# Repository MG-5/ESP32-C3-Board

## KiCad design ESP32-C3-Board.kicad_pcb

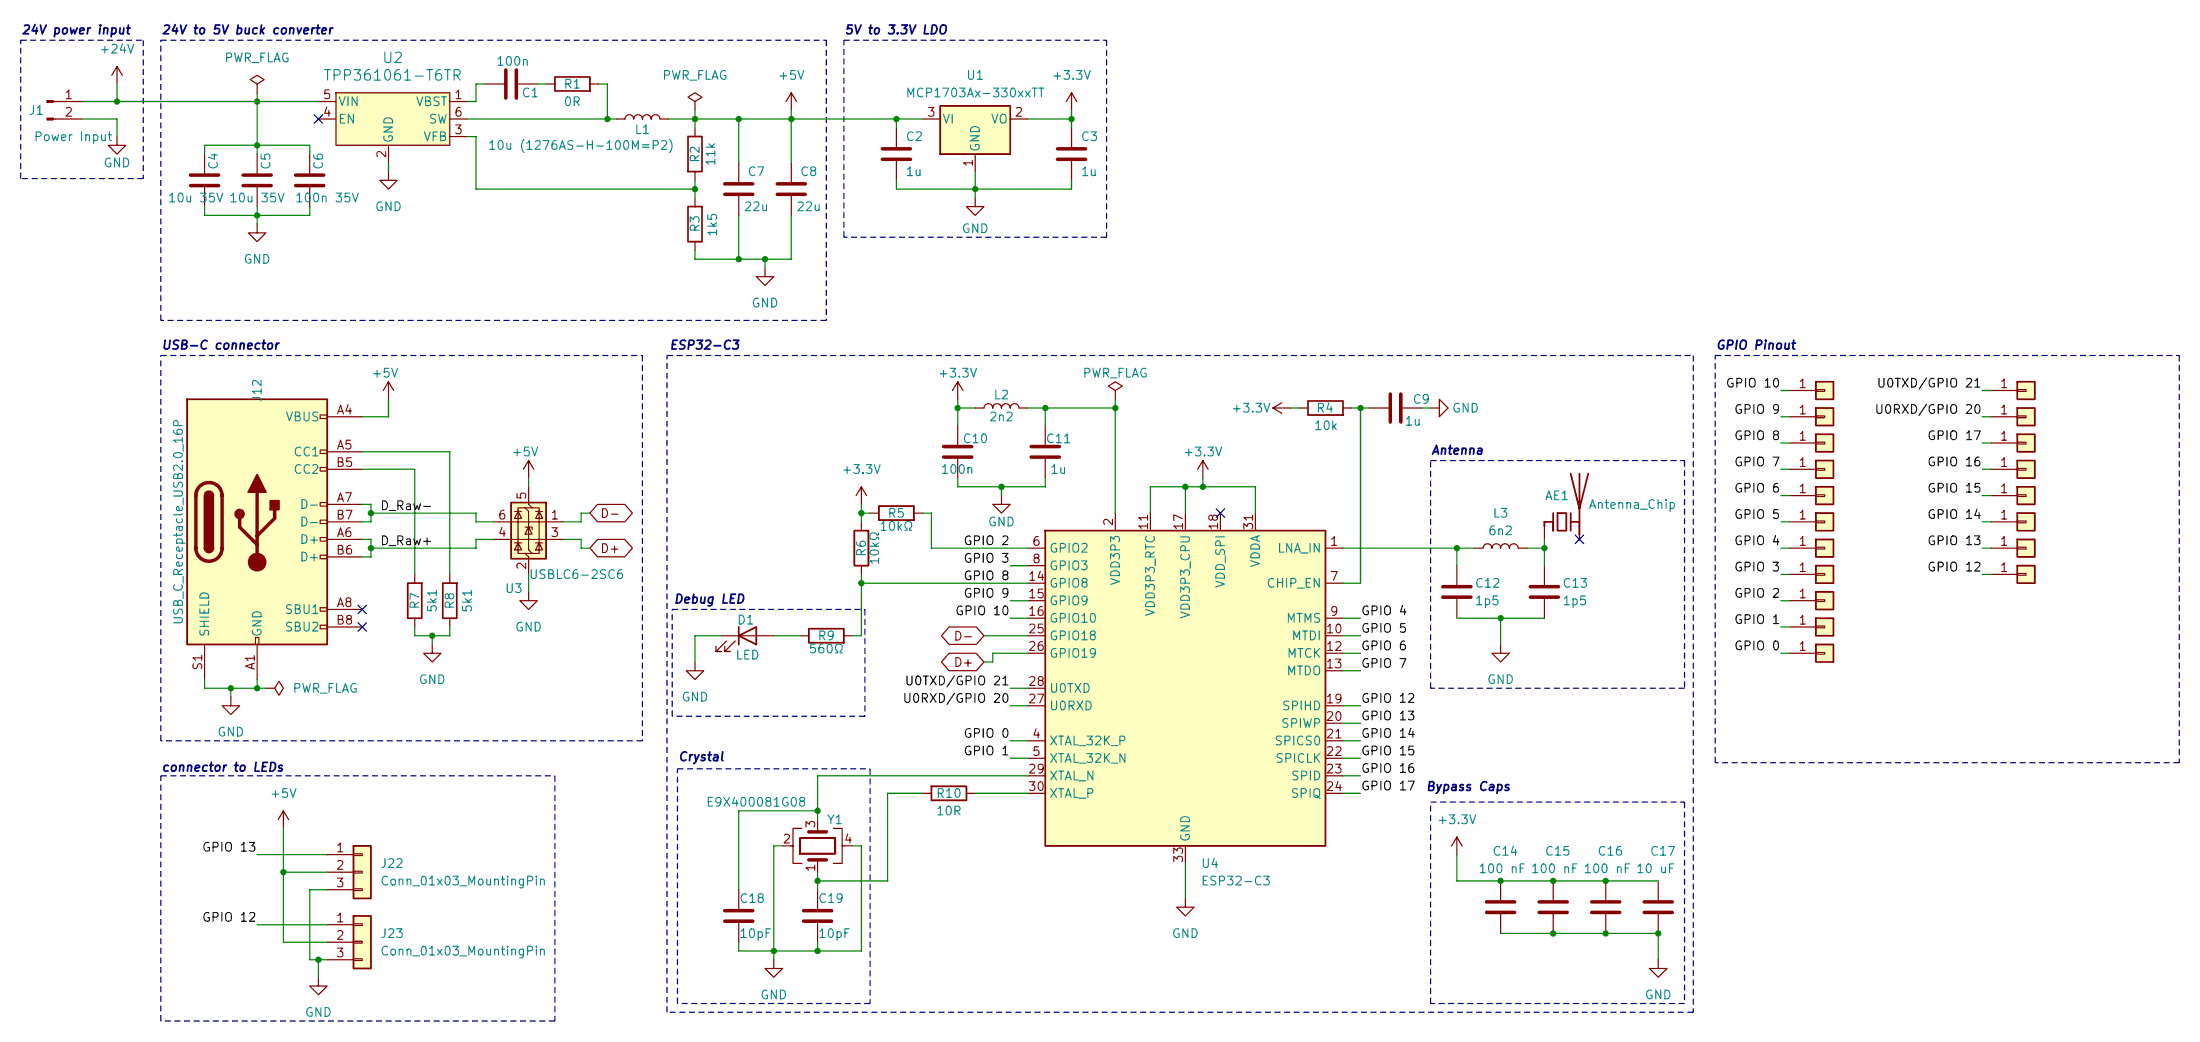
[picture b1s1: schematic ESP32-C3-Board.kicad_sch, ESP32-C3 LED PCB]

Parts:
AE1: Antenna_Chip; Johanson_2450AT43F0100
C1, C10: 100n; C_0603_1608Metric_Pad1.08x0.95mm_HandSolder
C2, C3, C9, C11: 1u; C_0603_1608Metric_Pad1.08x0.95mm_HandSolder
C4, C5: 10u 35V; C_0603_1608Metric_Pad1.08x0.95mm_HandSolder
C6: 100n 35V; C_0603_1608Metric_Pad1.08x0.95mm_HandSolder
C7, C8: 22u; C_0805_2012Metric_Pad1.18x1.45mm_HandSolder
C12, C13: 1p5; C_0402_1005Metric_Pad0.74x0.62mm_HandSolder
C14, C15, C16: 100 nF; C_0603_1608Metric_Pad1.08x0.95mm_HandSolder
C17: 10 uF; C_0603_1608Metric_Pad1.08x0.95mm_HandSolder
C18, C19: 10pF; C_0402_1005Metric_Pad0.74x0.62mm_HandSolder
D1: LED; LED_0805_2012Metric_Pad1.15x1.40mm_HandSolder
J1: Power Input; Molex_PicoBlade_53047-0210_1x02_P1.25mm_Vertical
J2, J3, J4, J5, J6, J7, J8, J9, J10, J11, J13, J14, J15, J16, J17, J18, J19, J20, J21: Conn_01x06; 01_P2.00mm
J12: USB_C_Receptacle_USB2.0_16P; USB_C_Receptacle_Palconn_UTC16-G
J22, J23: Conn_01x03_MountingPin; Molex_PicoBlade_53047-0310_1x03_P1.25mm_Vertical
L1: 10u (1276AS-H-100M=P2); L_1210_3225Metric_Pad1.42x2.65mm_HandSolder
L2: 2n2; L_0603_1608Metric
L3: 6n2; L_0402_1005Metric_Pad0.77x0.64mm_HandSolder
R1: 0R; R_0603_1608Metric_Pad0.98x0.95mm_HandSolder
R2: 11k; R_0603_1608Metric_Pad0.98x0.95mm_HandSolder
R3: 1k5; R_0603_1608Metric_Pad0.98x0.95mm_HandSolder
R4: 10k; R_0603_1608Metric_Pad0.98x0.95mm_HandSolder
R5, R6: 10kΩ; R_0603_1608Metric_Pad0.98x0.95mm_HandSolder
R7, R8: 5k1; R_0603_1608Metric_Pad0.98x0.95mm_HandSolder
R9: 560Ω; R_0603_1608Metric_Pad0.98x0.95mm_HandSolder
R10: 10R; R_0603_1608Metric_Pad0.98x0.95mm_HandSolder
U1: MCP1703Ax-330xxTT; SOT-23
U2: TPP361061-T6TR; SOT-23-6
U3: USBLC6-2SC6; SOT-23-6
U4: ESP32-C3; QFN-32-1EP_5x5mm_P0.5mm_EP3.7x3.7mm
Y1: E9X400081G08; Crystal_SMD_2016-4Pin_2.0x1.6mm

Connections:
+3.3V: C3.1, C10.1, C14.1, C15.1, C16.1, C17.1, L2.1, R4.1, R5.1, R6.2, U1.2 (VO), U4.11 (VDD3P3_RTC), U4.17 (VDD3P3_CPU), U4.31 (VDDA), U4.32 (VDDA)
+5V: C2.1, C7.2, C8.2, J12.A4 (VBUS), J12.A9 (VBUS), J12.B4 (VBUS), J12.B9 (VBUS), J22.2, J23.2, L1.1, R2.1, U1.3 (VI), U3.5 (VBUS)
+24V: C4.2, C5.2, C6.2, J1.1, U2.5 (VIN)
/D_Raw+: J12.A6 (D+), J12.B6 (D+), U3.4 (I/O2)
/D_Raw-: J12.A7 (D-), J12.B7 (D-), U3.6 (I/O1)
/GPIO 0: J21.1, U4.4 (XTAL_32K_P)
/GPIO 1: J20.1, U4.5 (XTAL_32K_N)
/GPIO 2: J19.1, R5.2, U4.6 (GPIO2)
/GPIO 3: J17.1, U4.8 (GPIO3)
/GPIO 4: J15.1, U4.9 (MTMS)
/GPIO 5: J13.1, U4.10 (MTDI)
/GPIO 6: J10.1, U4.12 (MTCK)
/GPIO 7: J8.1, U4.13 (MTDO)
/GPIO 8: J6.1, R6.1, R9.2, U4.14 (GPIO8)
/GPIO 9: J4.1, U4.15 (GPIO9)
/GPIO 10: J2.1, U4.16 (GPIO10)
/GPIO 12: J18.1, J23.1, U4.19 (SPIHD)
/GPIO 13: J16.1, J22.1, U4.20 (SPIWP)
/GPIO 14: J14.1, U4.21 (SPICS0)
/GPIO 15: J11.1, U4.22 (SPICLK)
/GPIO 16: J9.1, U4.23 (SPID)
/GPIO 17: J7.1, U4.24 (SPIQ)
/U0RXD/GPIO 20: J5.1, U4.27 (U0RXD)
/U0TXD/GPIO 21: J3.1, U4.28 (U0TXD)
D+: U3.3 (I/O2), U4.26 (GPIO19)
D-: U3.1 (I/O1), U4.25 (GPIO18)
GND: C2.2, C3.2, C4.1, C5.1, C6.1, C7.1, C8.1, C9.2, C10.2, C11.2, C12.2, C13.2, C14.2, C15.2, C16.2, C17.2, C18.2, C19.2, D1.1 (K), J1.2, J12.A1 (GND), J12.A12 (GND), J12.B1 (GND), J12.B12 (GND), J12.S1 (SHIELD), J22.3, J23.3, R3.1, R7.1, R8.1, U1.1 (GND), U2.2 (GND), U3.2 (GND), U4.33 (GND), Y1.2, Y1.4
unnamed: AE1.1 (FEED), C13.1, L3.2
unnamed: C1.2, R1.1
unnamed: C11.1, L2.2, U4.2 (VDD3P3), U4.3 (VDD3P3)
unnamed: C19.1, R10.2, Y1.1
unnamed: D1.2 (A), R9.1
unnamed: J12.A5 (CC1), R8.2
unnamed: J12.B5 (CC2), R7.2
unnamed: L1.2, R1.2, U2.6 (SW)
unnamed: C1.1, U2.1 (VBST)
unnamed: R2.2, R3.2, U2.3 (VFB)
unnamed: C9.1, R4.2, U4.7 (CHIP_EN)
unnamed: C12.1, L3.1, U4.1 (LNA_IN)
unnamed: C18.1, U4.29 (XTAL_N), Y1.3
unnamed: R10.1, U4.30 (XTAL_P)

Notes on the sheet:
Antenna
GPIO Pinout
Bypass Caps
Crystal
24V to 5V buck converter
USB-C connector
connector to LEDs
Debug LED
ESP32-C3
5V to 3.3V LDO
24V power input

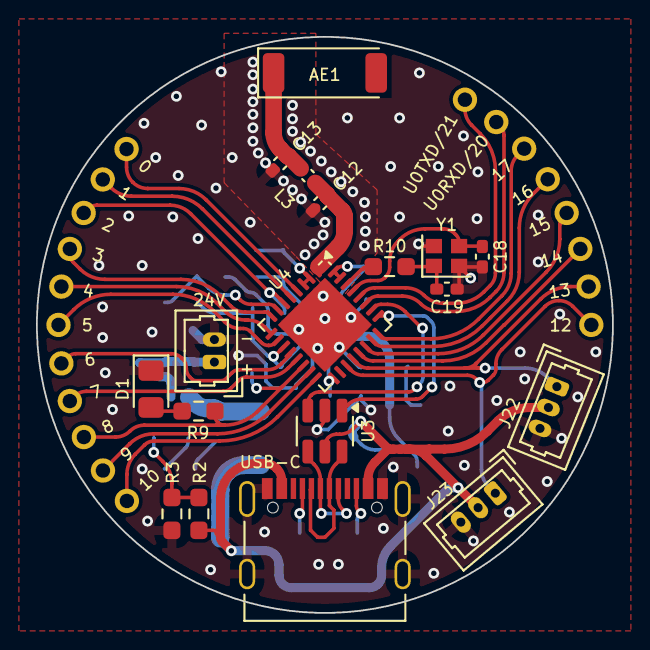
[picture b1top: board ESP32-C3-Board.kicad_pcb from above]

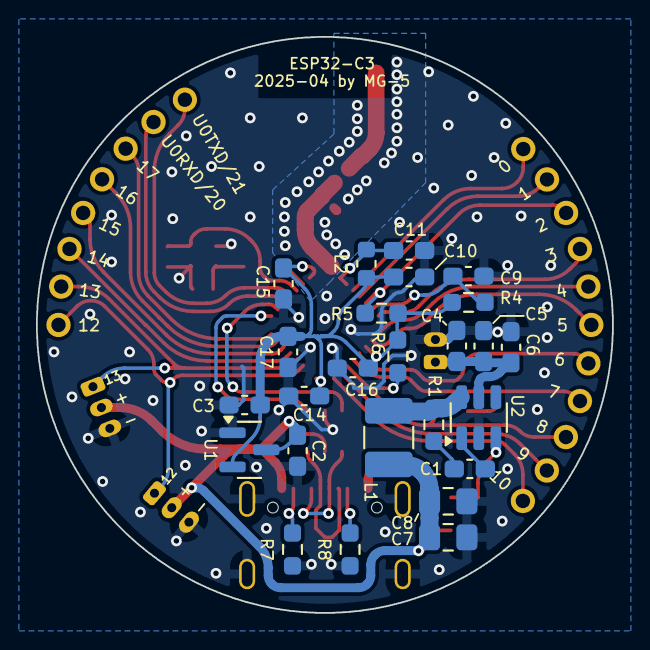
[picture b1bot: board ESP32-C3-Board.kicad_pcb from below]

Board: 2 copper layers, 32.0 x 32.0 mm, 62 parts (25 on the bottom side), 41 nets.

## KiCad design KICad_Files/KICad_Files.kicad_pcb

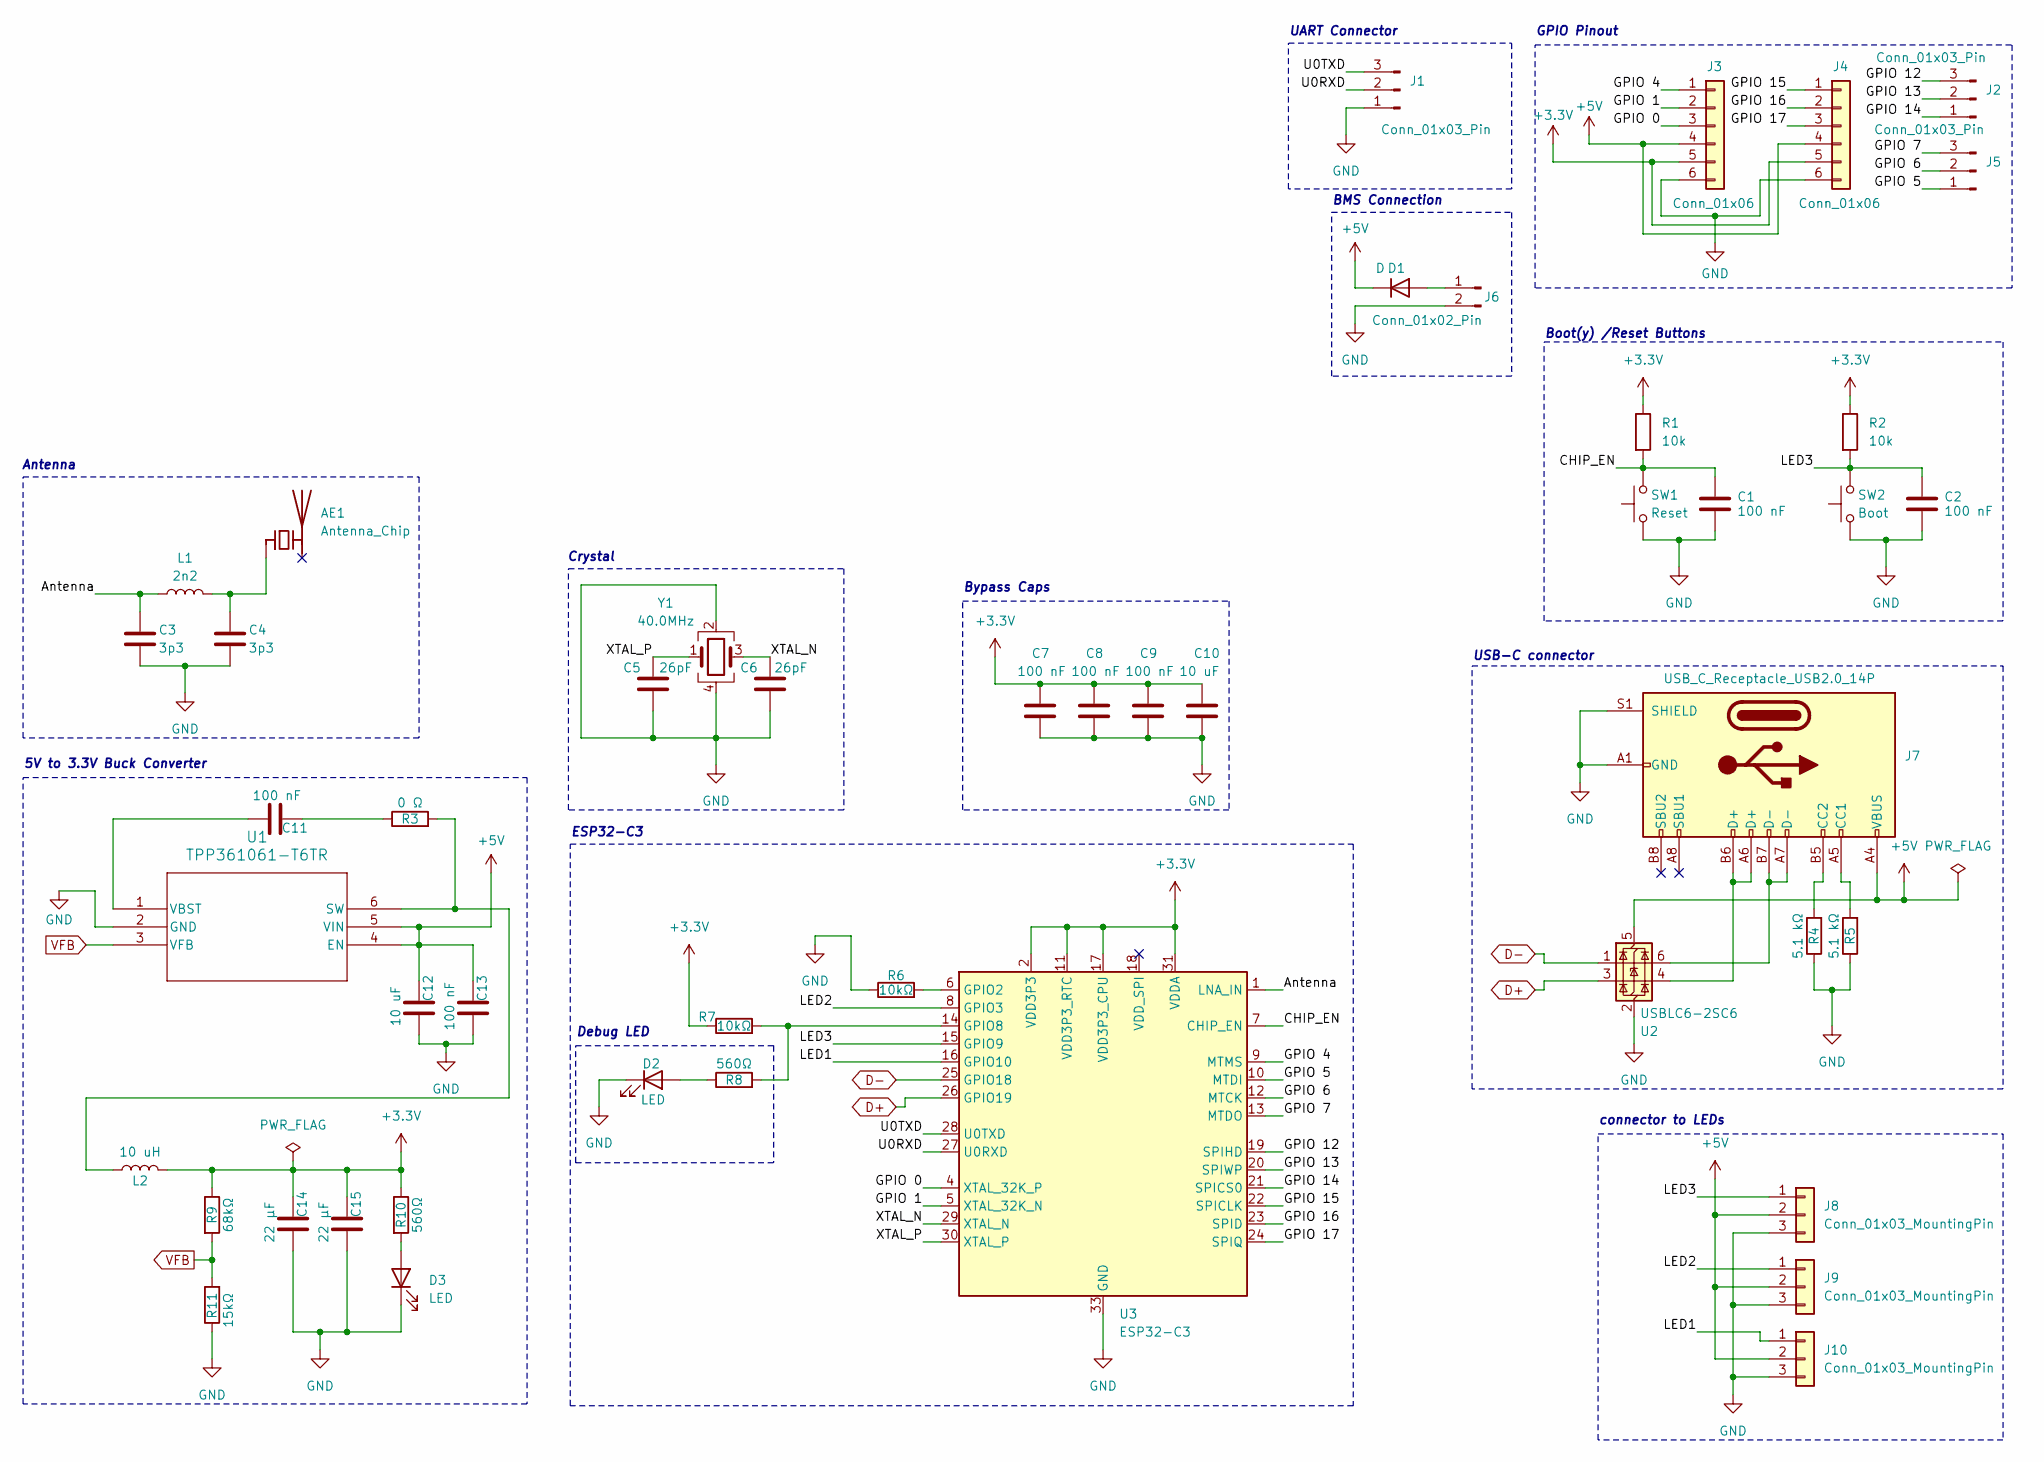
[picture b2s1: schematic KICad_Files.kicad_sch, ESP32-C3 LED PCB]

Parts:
AE1: Antenna_Chip; Johanson_2450AT43F0100
C1, C2, C7, C8, C9, C11, C13: 100 nF; C_0603_1608Metric_Pad1.08x0.95mm_HandSolder
C3, C4: 3p3; C_0603_1608Metric_Pad1.08x0.95mm_HandSolder
C5, C6: 26pF; C_0603_1608Metric_Pad1.08x0.95mm_HandSolder
C10, C12: 10 uF; C_0603_1608Metric_Pad1.08x0.95mm_HandSolder
C14, C15: 22 μF; C_0603_1608Metric_Pad1.08x0.95mm_HandSolder
D1: D; D_0603_1608Metric_Pad1.05x0.95mm_HandSolder
D2, D3: LED; LED_0805_2012Metric_Pad1.15x1.40mm_HandSolder
J1: Conn_01x03_Pin; PinHeader_1x03_P1.00mm_Vertical
J2, J5: Conn_01x03_Pin; PinHeader_1x03_P2.00mm_Vertical
J3, J4: Conn_01x06; PinHeader_1x06_P2.00mm_Vertical
J6: Conn_01x02_Pin; PinHeader_1x02_P2.00mm_Vertical
J7: USB_C_Receptacle_USB2.0_14P; USB_C_Receptacle_Palconn_UTC16-G
J8, J9, J10: Conn_01x03_MountingPin; Molex_PicoBlade_53047-0310_1x03_P1.25mm_Vertical
L1: 2n2; L_0603_1608Metric
L2: 10 uH; L_1008_2520Metric_Pad1.43x2.20mm_HandSolder
R1, R2: 10k; R_0603_1608Metric_Pad0.98x0.95mm_HandSolder
R3: 0 Ω; R_0603_1608Metric_Pad0.98x0.95mm_HandSolder
R4, R5: 5.1 kΩ; R_0603_1608Metric_Pad0.98x0.95mm_HandSolder
R6, R7: 10kΩ; R_0603_1608Metric_Pad0.98x0.95mm_HandSolder
R8, R10: 560Ω; R_0603_1608Metric_Pad0.98x0.95mm_HandSolder
R9: 68kΩ; R_0603_1608Metric_Pad0.98x0.95mm_HandSolder
R11: 15kΩ; R_0603_1608Metric_Pad0.98x0.95mm_HandSolder
SW1: Reset; RKB2SJK250SMTR LFS
SW2: Boot; RKB2SJK250SMTR LFS
U1: TPP361061-T6TR; SOT-23-6
U2: USBLC6-2SC6; SOT-23-6
U3: ESP32-C3; QFN-32-1EP_5x5mm_P0.5mm_EP3.7x3.7mm
Y1: 40.0MHz; Crystal_SMD_3225-4Pin_3.2x2.5mm

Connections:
+3.3V: C7.1, C8.1, C9.1, C10.1, C14.2, C15.2, J3.5, J4.5, L2.1, R1.1, R2.1, R7.1, R9.1, R10.1, U3.2 (VDD3P3), U3.3 (VDD3P3), U3.11 (VDD3P3_RTC), U3.17 (VDD3P3_CPU), U3.31 (VDDA), U3.32 (VDDA)
+5V: C12.2, C13.2, D1.1 (K), J3.4, J4.4, J7.A4 (VBUS), J7.A9 (VBUS), J7.B4 (VBUS), J7.B9 (VBUS), J8.2, J9.2, J10.2, U1.4 (EN), U1.5 (VIN), U2.5 (VBUS)
/Antenna: C3.1, L1.1, U3.1 (LNA_IN)
/CHIP_EN: C1.1, R1.2, SW1.2, U3.7 (CHIP_EN)
/GPIO 0: J3.3, U3.4 (XTAL_32K_P)
/GPIO 1: J3.2, U3.5 (XTAL_32K_N)
/GPIO 4: J3.1, U3.9 (MTMS)
/GPIO 5: J5.1, U3.10 (MTDI)
/GPIO 6: J5.2, U3.12 (MTCK)
/GPIO 7: J5.3, U3.13 (MTDO)
/GPIO 12: J2.3, U3.19 (SPIHD)
/GPIO 13: J2.2, U3.20 (SPIWP)
/GPIO 14: J2.1, U3.21 (SPICS0)
/GPIO 15: J4.1, U3.22 (SPICLK)
/GPIO 16: J4.2, U3.23 (SPID)
/GPIO 17: J4.3, U3.24 (SPIQ)
/LED1: J10.1, U3.16 (GPIO10)
/LED2: J9.1, U3.8 (GPIO3)
/LED3: C2.1, J8.1, R2.2, SW2.2, U3.15 (GPIO9)
/U0RXD: J1.2, U3.27 (U0RXD)
/U0TXD: J1.3, U3.28 (U0TXD)
/XTAL_N: C6.1, U3.29 (XTAL_N), Y1.3
/XTAL_P: C5.1, U3.30 (XTAL_P), Y1.1
D+: U2.3 (I/O2), U3.26 (GPIO19)
D-: U2.1 (I/O1), U3.25 (GPIO18)
GND: C1.2, C2.2, C3.2, C4.2, C5.2, C6.2, C7.2, C8.2, C9.2, C10.2, C12.1, C13.1, C14.1, C15.1, D2.1 (K), D3.1 (K), J1.1, J3.6, J4.6, J6.2, J7.A1 (GND), J7.A12 (GND), J7.B1 (GND), J7.B12 (GND), J7.S1 (SHIELD), J8.3, J9.3, J10.3, R4.1, R5.1, R6.1, R11.1, SW1.1, SW2.1, U1.2 (GND), U2.2 (GND), U3.33 (GND), Y1.2, Y1.4
unnamed: AE1.1 (FEED), C4.1, L1.2
unnamed: C11.2, R3.1
unnamed: D1.2 (A), J6.1
unnamed: D2.2 (A), R8.1
unnamed: D3.2 (A), R10.2
unnamed: J7.A5 (CC1), R5.2
unnamed: J7.B5 (CC2), R4.2
unnamed: J7.A6 (D+), J7.B6 (D+), U2.4 (I/O2)
unnamed: J7.A7 (D-), J7.B7 (D-), U2.6 (I/O1)
unnamed: L2.2, R3.2, U1.6 (SW)
unnamed: C11.1, U1.1 (VBST)
unnamed: R6.2, U3.6 (GPIO2)
unnamed: R7.2, R8.2, U3.14 (GPIO8)
VFB: R9.2, R11.2, U1.3 (VFB)

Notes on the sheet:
UART Connector
Antenna
GPIO Pinout
Bypass Caps
Boot(y) /Reset Buttons
Crystal
5V to 3.3V Buck Converter
USB-C connector
connector to LEDs
Debug LED
ESP32-C3
BMS Connection

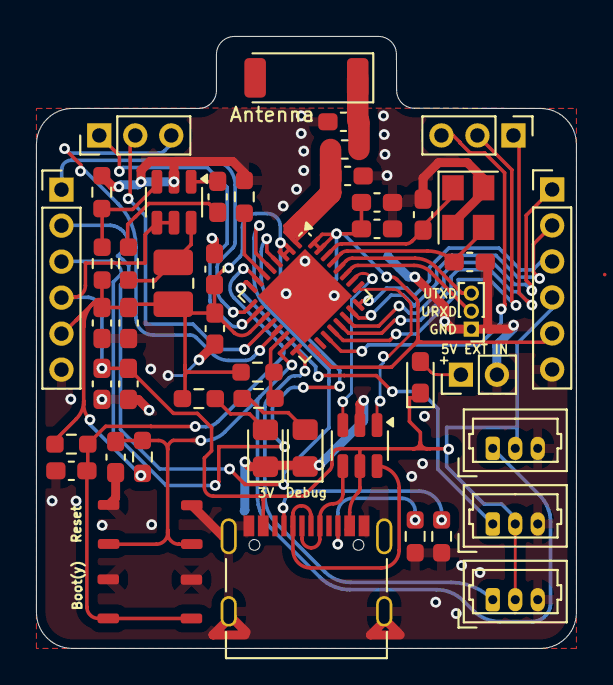
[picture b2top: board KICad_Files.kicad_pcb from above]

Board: 2 copper layers, 30.0 x 34.0 mm, 48 parts (0 on the bottom side), 40 nets.

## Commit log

2025-01-06 added KiCad files
2025-01-06 added board settings to the project file
2025-01-07 adjusted vias for better ground plane flow
2025-01-07 added more descriptions in the schematic
2025-01-07 switched R8/R9 to 10kOhm resistors and properly named switches for Boot/Reset
2025-01-26 rework of the PCB Layout
2025-01-27 fixed placement of silkscreen and improoved flow of the GND-plane
2025-01-27 added the correct values to the voltage divider
2025-01-27 Added silkscreen Logo and Credits
2025-01-27 generated files for production with JLCPCB and removed old production files
2025-02-11 added names for the GPIO moved resistors for 5V USB to the front plane changed Logo from Nettz39 e.V. zu BlindDeerStudio Naming of GPIOS are still generic
2025-02-12 Properly named all I/O Pins/ Power Pins on the Back fixed some minor errors where the silkscreen wasnt aligned properly
2025-02-13 Fixed Voltage Divider values in PCB Editor
2025-02-17 added multiple components for proper operation of the ESP added 40 mHz crystal added a connector for UART Changed LED placement to GPIO8 for use as Debug LED
2025-02-25 added footprints to the added parts
2025-02-25 Fixed ground connection to 5V error
2025-02-27 Complete rework of the PCB routing
2025-02-27 Fixed errors and silkscreen overlapping
2025-02-27 removed some loose tracks
2025-04-13 Redesign Add 24V buck converter
2025-04-13 Rename/move files
